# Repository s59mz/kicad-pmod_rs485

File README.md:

# kicad-pmod_rs485
PMOD PCB module for RS-485 Interface 

Schematic:
[kicad-pmod_rs485.pdf](kicad-pmod_rs485.pdf)

BOM:
[kicad-pmod_rs485.csv](kicad-pmod_rs485.csv)

Gerbers:
[gerbers.zip](https://github.com/s59mz/kicad-pmod_rs485/raw/main/gerbers.zip)

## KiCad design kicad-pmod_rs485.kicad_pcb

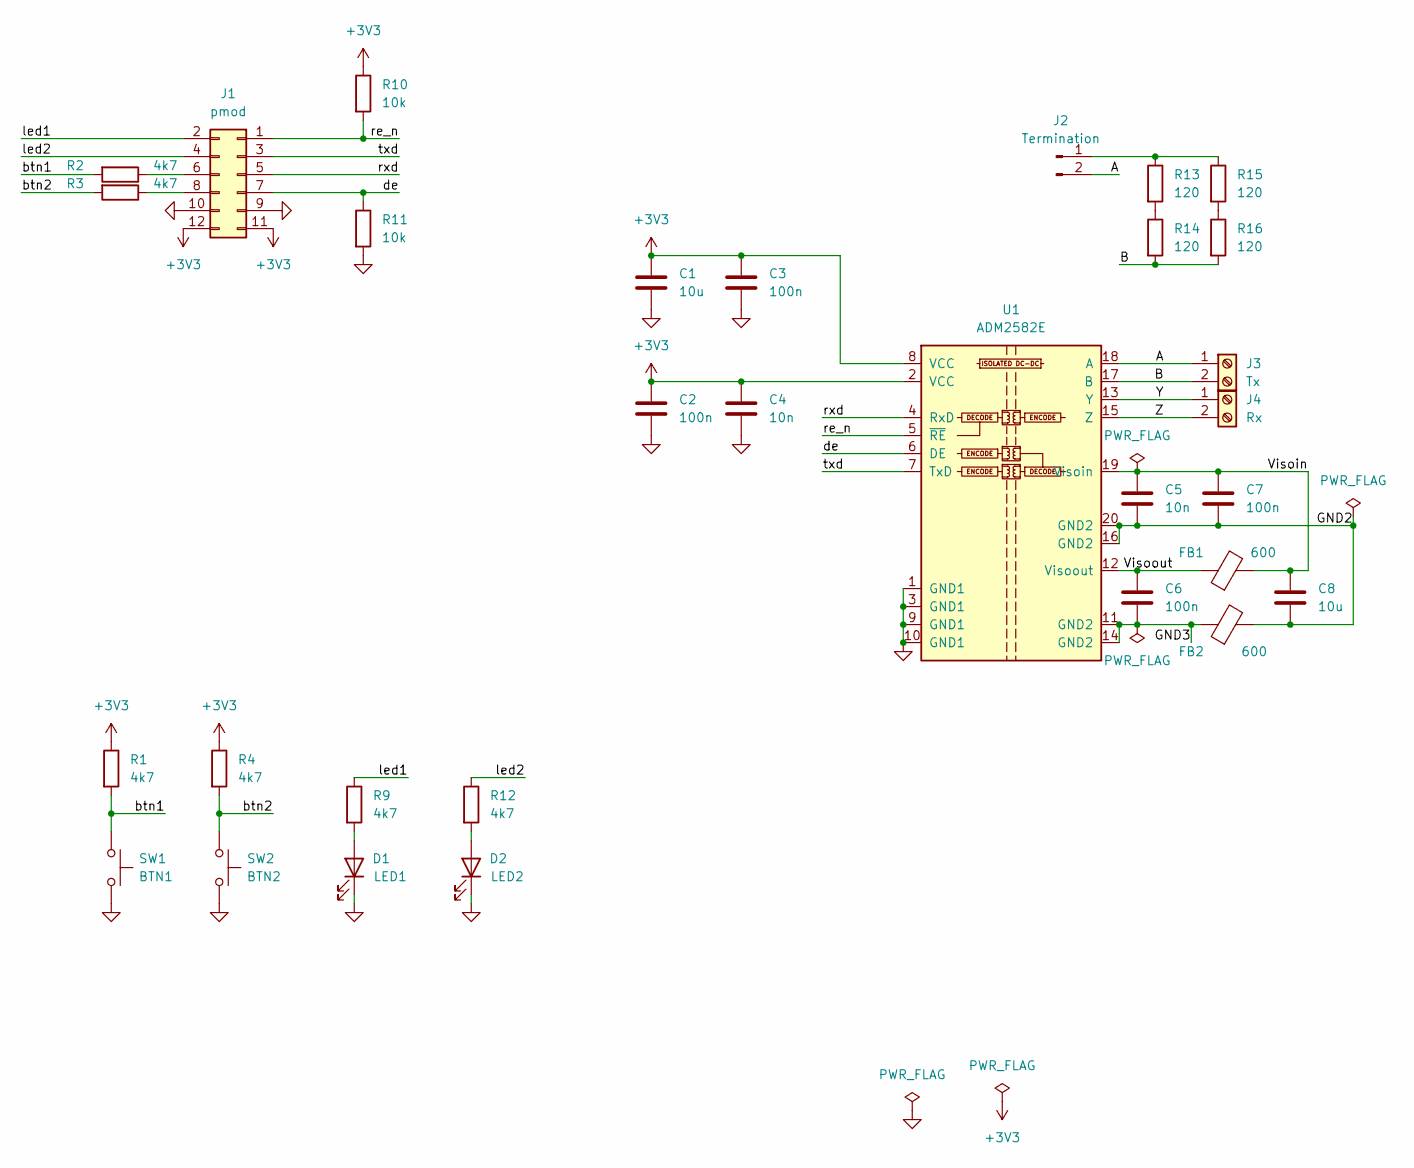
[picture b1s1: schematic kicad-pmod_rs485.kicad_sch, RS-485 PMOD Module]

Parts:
C1, C8: 10u; C_0603_1608Metric_Pad1.08x0.95mm_HandSolder
C2, C3, C6, C7: 100n; C_0603_1608Metric_Pad1.08x0.95mm_HandSolder
C4, C5: 10n; C_0603_1608Metric_Pad1.08x0.95mm_HandSolder
D1: LED1; LED_0603_1608Metric_Pad1.05x0.95mm_HandSolder
D2: LED2; LED_0603_1608Metric_Pad1.05x0.95mm_HandSolder
FB1, FB2: 600; L_0603_1608Metric_Pad1.05x0.95mm_HandSolder
J1: pmod; PinHeader_2x06_P2.54mm_Horizontal
J2: Termination; PinHeader_1x02_P2.54mm_Vertical
J3: Tx; TerminalBlock_bornier-2_P5.08mm
J4: Rx; TerminalBlock_bornier-2_P5.08mm
R1, R2, R3, R4, R9, R12: 4k7; R_0603_1608Metric_Pad0.98x0.95mm_HandSolder
R10, R11: 10k; R_0603_1608Metric_Pad0.98x0.95mm_HandSolder
R13, R14, R15, R16: 120; R_0603_1608Metric_Pad0.98x0.95mm_HandSolder
SW1: BTN1; SW_SPST_FSMSM
SW2: BTN2; SW_SPST_FSMSM
U1: ADM2582E; SOIC-20W_7.5x12.8mm_P1.27mm

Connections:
+3V3: C1.1, C2.1, C3.1, C4.1, J1.11, J1.12, R1.1, R4.1, R10.1, U1.2 (VCC), U1.8 (VCC)
/A: J2.2, J3.1, U1.18 (A)
/B: J3.2, R14.2, R16.2, U1.17 (B)
/GND2: C5.2, C7.2, C8.2, FB2.2, U1.16 (GND2), U1.20 (GND2)
/GND3: C6.2, FB2.1, U1.11 (GND2), U1.14 (GND2)
/Visoin: C5.1, C7.1, C8.1, FB1.2, U1.19 (Visoin)
/Visoout: C6.1, FB1.1, U1.12 (Visoout)
/Y: J4.1, U1.13 (Y)
/Z: J4.2, U1.15 (Z)
/btn1: R1.2, R2.2, SW1.1
/btn2: R3.2, R4.2, SW2.1
/de: J1.7, R11.1, U1.6 (DE)
/led1: J1.2, R9.1
/led2: J1.4, R12.1
/re_n: J1.1, R10.2, U1.5 (~RE)
/rxd: J1.5, U1.4 (RxD)
/txd: J1.3, U1.7 (TxD)
GND: C1.2, C2.2, C3.2, C4.2, D1.1 (K), D2.1 (K), J1.9, J1.10, R11.2, SW1.2, SW2.2, U1.1 (GND1), U1.3 (GND1), U1.9 (GND1), U1.10 (GND1)
unnamed: D1.2 (A), R9.2
unnamed: D2.2 (A), R12.2
unnamed: J1.6, R2.1
unnamed: J1.8, R3.1
unnamed: J2.1, R13.1, R15.1
unnamed: R13.2, R14.1
unnamed: R15.2, R16.1

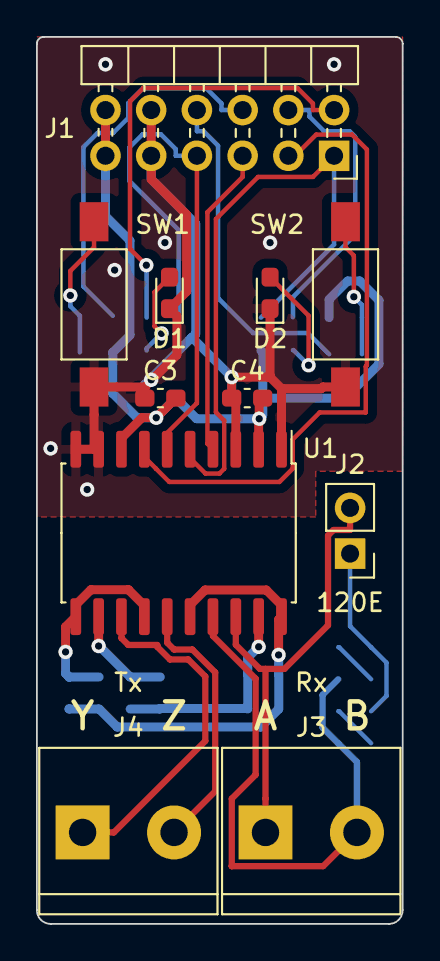
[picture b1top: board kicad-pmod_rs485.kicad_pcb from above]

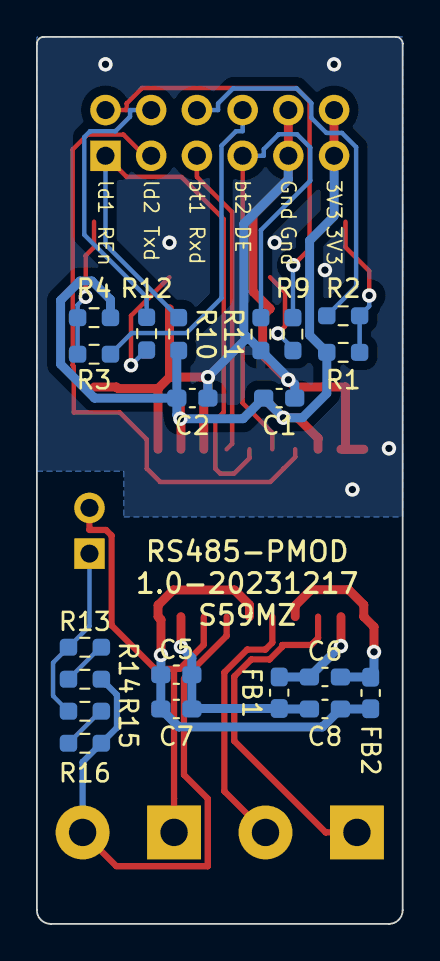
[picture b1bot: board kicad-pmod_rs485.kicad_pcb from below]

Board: 2 copper layers, 20.3 x 49.3 mm, 31 parts (20 on the bottom side), 25 nets.

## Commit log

2023-12-17 1.0 - jlcpcb
2023-12-17 readme
